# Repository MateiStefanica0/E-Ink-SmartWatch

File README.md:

## 1. Schema bloc

## 2. Descrierea functionalitatii hardware

Sistemul este proiectat in jurul microcontrolerului nRF52840, punand accent pe conectivitate stabila si conservarea energiei, utilizand o tehnologie de afisare E-Paper care permite vizibilitate excelenta in lumina solara cu un consum de curent extrem de mic in starea statica.

### 2.1. Nucleul Sistemului (MCU)
* **Microcontroler:** Nordic nRF52840.
* **Comunicatie:** Gestioneaza functionalitatile Bluetooth si perifericele prin I2C si SPI.
* **Radio:** Semnalul trece printr-o retea de filtrare catre o antena ceramica de 2.4GHz. Sub antena, PCB-ul este decupat pentru a nu bloca semnalul.

### 2.2. Management Energie
* **Incarcare:** Chip-ul BQ25180 gestioneaza incarcarea bateriei LiPo prin mufa USB-C.
* **Monitorizare:** MAX17048 masoara constant nivelul bateriei si transmite datele prin I2C.
* **Regulator:** RT6160A (Buck-Boost) asigura o tensiune constanta de 3.3V, chiar si cand bateria se descarca.

### 2.3. Afisaj si Feedback
* **Ecran E-Paper:** Conectat prin interfata SPI pentru consum minim (consuma energie doar cand schimba imaginea).
* **Circuit Drive:** Include tranzistori si diode pentru a genera tensiunile necesare refresh-ului ecranului.
* **Vibratii:** Driver-ul DRV2605 controleaza motorul haptic, oferind alerte tactile utilizatorului.

### 2.4. Senzori si Protectie
* **Miscare:** Senzorul BMA423 (IMU) este folosit pentru pedometru si detectarea gestului de ridicare a mainii.
* **Protectie USB:** Chip-ul USBLC6-2 protejeaza placa impotriva descarcarilor electrostatice de pe portul USB.

### 2.5. Calcule de consum (estimativ)
* **Sleep Mode:** Consumul sistemului este de aproximativ 2-5 uA (nRF52840 + IMU in low power).
I_sleep = MCU_off + IMU_low + FuelGauge + DC/DC = 1.5 + 7 + 23 + 2 = ~33.5 uA
* **Active Mode:** In timpul transferului de date sau refresh-ului ecranului, consumul poate urca la 5-12 mA.
I_active = MCU_active + IMU_active + EPD_refresh + Haptic = ~10mAh
* **Autonomie:** 
Presupunand ca dintr-o ora, ceasul e activ 2 minute si in standby 58 de minute:
I_mediu = ( (I_active * 2 min) + (I_sleep * 58 min)) / 60 min = ~365 uA

Deci, autonomia e capacitatea_bateriei / I_mediu = 100mAh / 365uA = ~274 ore

## 3. Alocarea Pinilor nRF52840 (Pin Mapping)

Configuratia pinilor a fost aleasa pentru a optimiza rutarea pe PCB si pentru a respecta cerintele perifericelor. Toti pinii sunt configurati in firmware conform tabelului:

| Functie / Periferic | Semnal (Net) | Pin MCU | Explicatie |
| :--- | :--- | :--- | :--- |
| **I2C Bus (SCL)** | `I2C_SCL` | **P0.27** | Bus comun: IMU, Fuel Gauge, Haptic, PMIC. |
| **I2C Bus (SDA)** | `I2C_SDA` | **P0.26** | Bus comun: IMU, Fuel Gauge, Haptic, PMIC. |
| **SPI (SCK)** | `EPD_SCK` | **P0.31** | Ceas pentru transfer date catre ecran. |
| **SPI (MOSI)** | `EPD_MOSI` | **P0.29** | Date imagini catre ecran. |
| **EPD Control** | `EPD_BUSY` | **P0.05** | Indica daca ecranul este ocupat. |
| **EPD Control** | `EPD_RST` | **P0.06** | Reset hardware pentru ecran. |
| **EPD Control** | `EPD_DC` | **P0.08** | Selectie Date sau Comenzi (Data/Command). |
| **Butoane** | `SW_UP` | **P0.11** | Buton SUS (navigare). |
| **Butoane** | `SW_ENT` | **P0.12** | Buton SELECT (confirmare). |
| **Butoane** | `SW_DN` | **P0.14** | Buton JOS (navigare). |
| **Haptic Feedback**| `EN_HAPTIC` | **P0.17** | Activare driver vibratii. |
| **Senzor IMU** | `IMU_INT1` | **P0.19** | Intrerupere pentru detectare miscare. |
| **Debug/Prog** | `SWDIO` | `SWDIO` | Programare si depanare. |
| **Debug/Prog** | `SWCLK` | `SWCLK` | Ceas programare. |

---

## 4. Detalii de Design (Design Log)

### 4.1. Implementare PCB
* **Antena RF:** Plasata pe margine, cu zona de sub ea libera (fara cupru) pentru semnal Bluetooth bun.
* **Grosime:** PCB-ul are 1.0mm grosime pentru a incapea in carcasa InkTime si am ales ca rutarea sa fie pe 4 layere: unul de GND, unul de Power, unul de top si unul de bottom.
* **Filtrare:** Condensatorii de 100nF sunt pusi cat mai aproape de pinii de alimentare ai chip-urilor.
* **Trasee:** Puterea are latime de 0.3mm, iar semnalele de date 0.15mm.
* **Abordare:** Initial, am incercat sa fac autorutare, dar nu a functionat, asa ca apoi am aranjat componentele pe placa pentru a fi cat mai putine fire intre pini indepartati, apoi am rutat semnalele care nu sunt de putere, apoi pe cele de putere, iar la final am pus polygon pour si am tras si ultimele fire de GND ramase.

### 4.2. Carcasa si Erori
* **Aliniere:** Butoanele si mufa USB-C sunt puse exact unde sunt gaurile in carcasa data.
* **Erori permise:** Erorile de tip "Dimension" de la USB si butoane sunt ignorate conform cerintelor proiectului. 
* **Erori ERC:** Singurele erori care au ramas sunt cele legate de pinii de care nu am legat nimic.
* **Erori DRC:** Erorile pe care le-am admis sunt cele cauzate de fire care trec printre alti pini ai microcontrollerului (asta nu se poate evita) sau viasuri care sunt prea apropiate din acelasi motiv.

## 5. Tabel BOM (Bill of Materials)

Mai jos sunt prezentate componentele principale necesare pentru asamblarea ceasului InkTime. Codurile de produs sunt optimizate pentru serviciul de asamblare JLC PCB.

| Designator | Componenta | Descriere / Parametri | Link Achizitie | Datasheet |
| :--- | :--- | :--- | :--- | :--- |
| U1 | **nRF52840** | MCU Bluetooth 5.4, ARM Cortex-M4F | [Link JLC](https://jlcpcb.com/partdetail/NordicSemicon-NRF52840_QIAAR/C190794) | [Datasheet](https://www.lcsc.com/datasheet/lcsc_datasheet_2304140030_Nordic-Semicon-NRF52840-QIAA-R_C190794.pdf) |
| U2 | **BQ25180YBGR** | IC Incarcare Baterie LiPo (I2C) | [Link JLC](https://jlcpcb.com/partdetail/TexasInstruments-BQ25180YBGR/C3682423) | [Datasheet](https://www.ti.com/cn/lit/gpn/bq25180) |
| U3 | **MAX17048G+T10**| Fuel Gauge (Monitorizare baterie) | [Link JLC](https://jlcpcb.com/partdetail/2777647-MAX17048GT10/C2682616) | [Datasheet](https://www.lcsc.com/datasheet/lcsc_datasheet_2410121738_Analog-Devices-Inc--Maxim-Integrated-MAX17048G-T10_C2682616.pdf) |
| IC1 | **RT6160AWSC** | Regulator Buck-Boost 3.3V | [Link JLC](https://jlcpcb.com/partdetail/RichtekTech-RT6160AWSC/C7065276) | [Datasheet](https://wmsc.lcsc.com/wmsc/upload/file/pdf/v2/lcsc/2312271436_Richtek-Tech-RT6160AWSC_C7065276.pdf) |
| IC2 | **BMA423** | Accelerometru 3 axe (IMU) | [Link JLC](https://jlcpcb.com/partdetail/BoschSensortec-BMA423/C189517) | [Datasheet](https://www.lcsc.com/datasheet/lcsc_datasheet_1810010040_Bosch-Sensortec-BMA423_C189517.pdf) |
| IC3 | **DRV2605YZFR** | Driver Motor Haptic (LRA/ERM) | [Link JLC](https://jlcpcb.com/partdetail/TexasInstruments-DRV2605YZFR/C81079) | [Datasheet](https://jlcpcb.com/partdetail/TexasInstruments-DRV2605YZFR/C81079) |
| ANT1 | **2450AT18B100E**| Antena Ceramica 2.4GHz | [Link JLC](https://jlcpcb.com/partdetail/JohansonDielectrics-2450AT18B100E/C2917717) | [Datasheet](https://www.lcsc.com/datasheet/lcsc_datasheet_2404021210_Johanson-Dielectrics-2450AT18B100E_C2917717.pdf) |
| J1 | **KH-TYPE-C-16P** | Conector USB Type-C 16 pini | [Link JLC](https://jlcpcb.com/partdetail/Shenzhen_KinghelmElec-KH_TYPE_C16P/C709357) | [Datasheet](https://jlcpcb.com/partdetail/Shenzhen_KinghelmElec-KH_TYPE_C16P/C709357) |
| J2 | **503480-2400** | Conector FPC 24 pini (E-Paper) | [Link JLC](https://jlcpcb.com/parts/componentSearch?searchTxt=503480-2400) | [Datasheet](https://www.molex.com/content/dam/molex/molex-dot-com/products/automated/en-us/salesdrawingpdf/503/503480/5034802400_sd.pdf?inline) |
| C_dec | **Condensator 100nF** | 0201, X5R, 6.3V (Decuplare generala) | [Link JLC](https://jlcpcb.com/partdetail/SamsungElectroMechanics-CL03A104KQ3NNNC/C1613) | [Datasheet](https://datasheet.lcsc.com/lcsc/1811141213_Samsung-Electro-Mechanics-CL03A104KQ3NNNC_C1613.pdf) |
| C_bulk | **Condensator 10uF** | 0402, X5R, 10V (Filtrare alimentare) | [Link JLC](https://jlcpcb.com/partdetail/MurataElectronics-GRM155R61A106ME11D/C155255) | [Datasheet](https://datasheet.lcsc.com/lcsc/1811011516_Murata-Electronics-GRM155R61A106ME11D_C155255.pdf) |
| R_pu | **Rezistenta 4.7k** | 0201, 1/20W (Pull-up I2C/Butoane) | [Link JLC](https://jlcpcb.com/partdetail/Yageo-RC0201JR074K7L/C13032) | [Datasheet](https://datasheet.lcsc.com/lcsc/1811021213_Yageo-RC0201JR-074K7L_C13032.pdf) |
| L_pwr | **Inductor 1.0uH** | 0805, 2.1A (Pentru RT6160A/Buck-Boost) | [Link JLC](https://jlcpcb.com/partdetail/Sunlord-MWSA0503S1R0MT/C2915000) | [Datasheet](https://datasheet.lcsc.com/lcsc/2203151500_Sunlord-MWSA0503S-1R0MT_C2915000.pdf) |
| X_32k | **Cristal 32.768kHz** | 1.6x1.0mm, 9pF (Pentru Sleep Mode nRF) | [Link JLC](https://jlcpcb.com/partdetail/YangzhouYangjieElectronic-FC1610AN32_7680KA_A/C147814) | [Datasheet](https://datasheet.lcsc.com/lcsc/1811141221_Epson-FC-1610-32-7680KA-A3_C147814.pdf) |
| D_esd | **USBLC6-2P6** | Protectie ESD USB (SOT-666) | [Link JLC](https://jlcpcb.com/partdetail/STMicroelectronics-USBLC62P6/C7519) | [Datasheet](https://www.st.com/resource/en/datasheet/usblc6-2.pdf) |

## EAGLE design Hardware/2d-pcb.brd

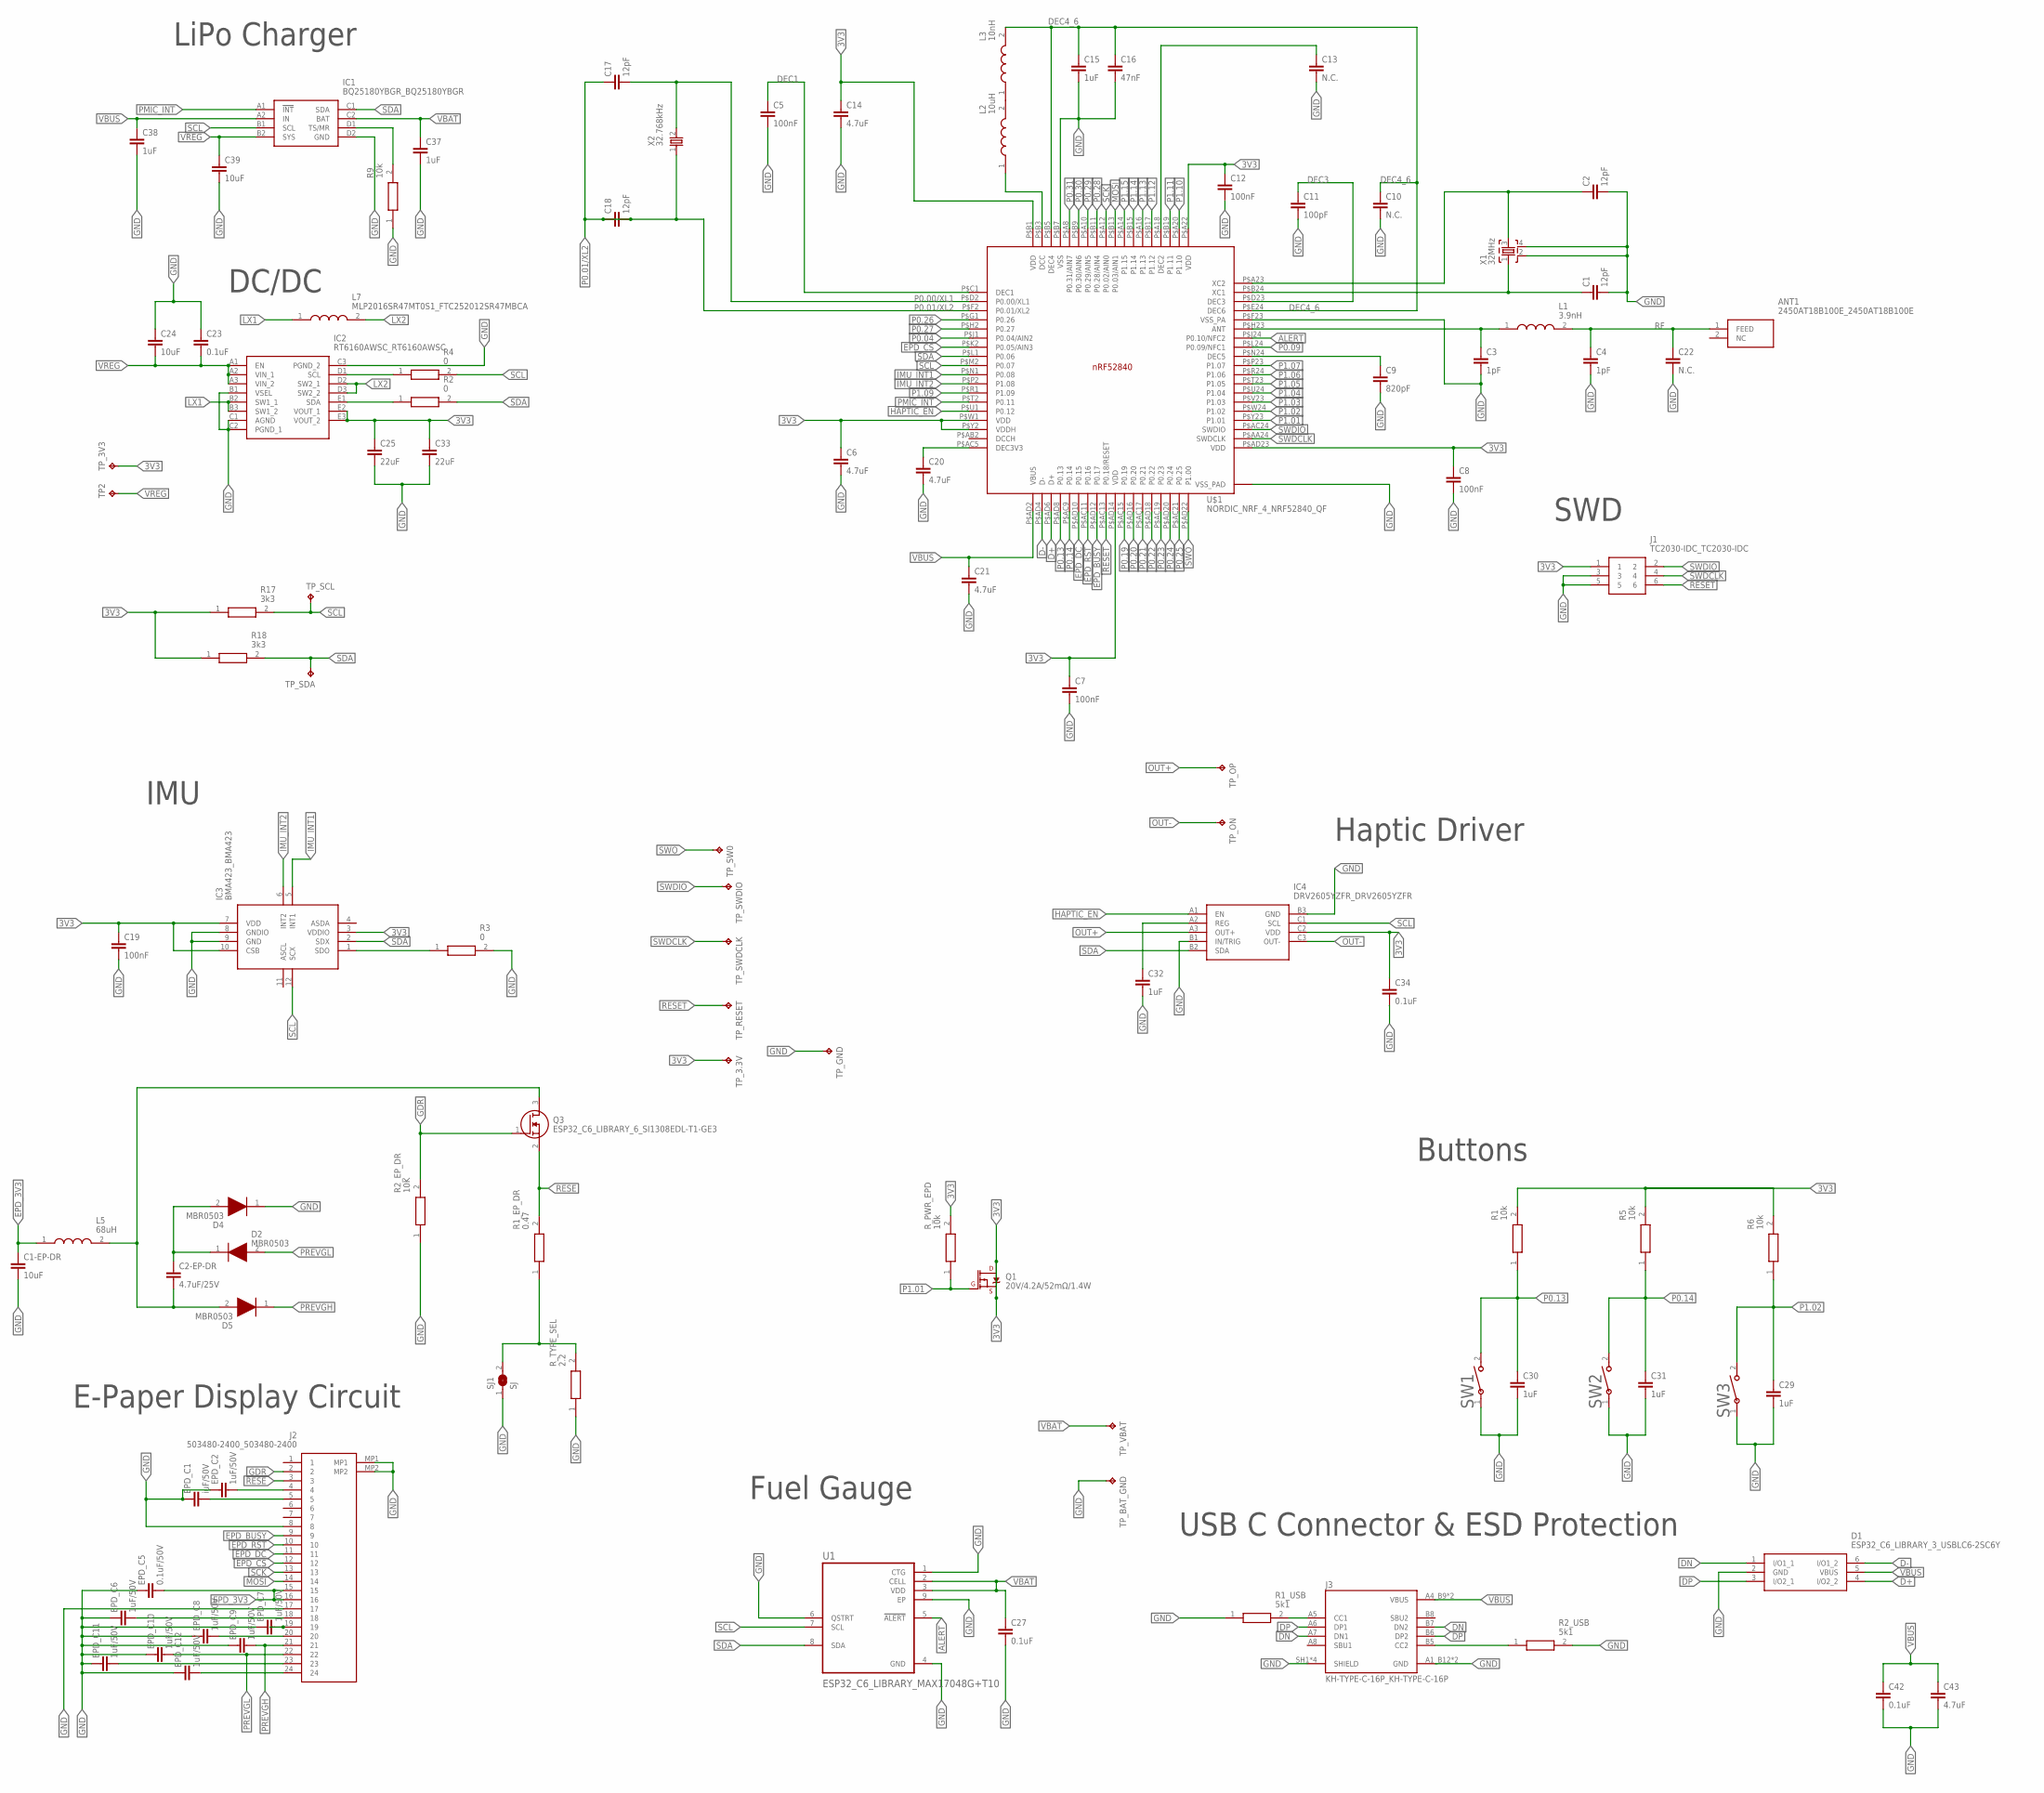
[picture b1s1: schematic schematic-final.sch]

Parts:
ANT1: 2450AT18B100E_2450AT18B100E; 2450AT18B100E_ANTC3216X140N
C1, C2, C17, C18: 12pF; ESP32_C6_LIBRARY_1_ESP32_WROVER_EAGLE-LTSPICE_C0402
C1-EP-DR, C24, C39: 10uF; ESP32_C6_LIBRARY_1_ESP32_WROVER_EAGLE-LTSPICE_C0402
C2-EP-DR: 4.7uF/25V; ESP32_C6_LIBRARY_1_ESP32_WROVER_EAGLE-LTSPICE_C0402
C3, C4: 1pF; ESP32_C6_LIBRARY_1_ESP32_WROVER_EAGLE-LTSPICE_C0402
C5, C7, C8, C12, C19: 100nF; NORDIC_NRF_3_RESC0201_L
C6, C14, C20, C21, C43: 4.7uF; ESP32_C6_LIBRARY_1_ESP32_WROVER_EAGLE-LTSPICE_C0402
C9: 820pF; ESP32_C6_LIBRARY_1_ESP32_WROVER_EAGLE-LTSPICE_C0402
C10, C13, C22: N.C.; ESP32_C6_LIBRARY_1_ESP32_WROVER_EAGLE-LTSPICE_C0402
C11: 100pF; ESP32_C6_LIBRARY_1_ESP32_WROVER_EAGLE-LTSPICE_C0402
C15, C29, C30, C31, C32, C37, C38: 1uF; ESP32_C6_LIBRARY_1_ESP32_WROVER_EAGLE-LTSPICE_C0402
C16: 47nF; ESP32_C6_LIBRARY_1_ESP32_WROVER_EAGLE-LTSPICE_C0402
C23, C27, C34, C42: 0.1uF; ESP32_C6_LIBRARY_1_ESP32_WROVER_EAGLE-LTSPICE_C0402
C25, C33: 22uF; ESP32_C6_LIBRARY_1_ESP32_WROVER_EAGLE-LTSPICE_C0402
D1: ESP32_C6_LIBRARY_3_USBLC6-2SC6Y; ESP32_C6_LIBRARY_3_SOT95P280X145-6N
D2, D4, D5: MBR0503; ESP32_C6_LIBRARY_5_SOD3716X135N
EPD_C1: iuF/50V; ESP32_C6_LIBRARY_1_ESP32_WROVER_EAGLE-LTSPICE_C0402
EPD_C2, EPD_C6, EPD_C7, EPD_C8, EPD_C9, EPD_C10, EPD_C11, EPD_C12: 1uF/50V; ESP32_C6_LIBRARY_1_ESP32_WROVER_EAGLE-LTSPICE_C0402
EPD_C5: 0.1uF/50V; ESP32_C6_LIBRARY_1_ESP32_WROVER_EAGLE-LTSPICE_C0402
IC1: BQ25180YBGR_BQ25180YBGR; BQ25180YBGR_BGA8C40P2X4_100X155X50
IC2: RT6160AWSC_RT6160AWSC; RT6160AWSC_BGA15C40P3X5_140X230X60
IC3: BMA423_BMA423
IC4: DRV2605YZFR_DRV2605YZFR; DRV2605YZFR_BGA9C50P3X3_144X144X62
J1: TC2030-IDC_TC2030-IDC; TC2030-IDC_TC2030IDC
J2: 503480-2400_503480-2400; 503480-2400_5034802400
J3: KH-TYPE-C-16P_KH-TYPE-C-16P; KH-TYPE-C-16P_KINGHELM_KH-TYPE-C-16P
L1: 3.9nH; MLP2016SR47MT0S1_INDC2016X100N
L2: 10uH; MLP2016SR47MT0S1_INDC2016X100N
L3: 10nH; MLP2016SR47MT0S1_INDC2016X100N
L5: 68uH; MLP2016SR47MT0S1_INDC2016X100N
L7: MLP2016SR47MT0S1_FTC252012SR47MBCA; MLP2016SR47MT0S1_INDC2016X100N
Q1: 20V/4.2A/52mΩ/1.4W; ESP32_C6_LIBRARY_4_ESP32_C6_LIBRARY_4_ESP32_C6_LIBRARY_4_ES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
Q3: ESP32_C6_LIBRARY_6_SI1308EDL-T1-GE3; ESP32_C6_LIBRARY_6_SOT65P210X110-3N
R1, R5, R6: 10k; ERA-1AEB3401C_0201
R1_EP_DR: 0.47; ERA-1AEB3401C_0201
R1_USB, R2_USB: 5k1; ERA-1AEB3401C_0201
R2, R3, R4: 0; ERA-1AEB3401C_0201
R2_EP_DR: 10K; ERA-1AEB3401C_0201
R9: 10k; CPF0201D7K68C1_0201
R17, R18: 3k3; ERA-1AEB3401C_0201
R_PWR_EPD: 10k; ERA-1AEB3401C_0201
R_TYPE_SEL: 2.2; ERA-1AEB3401C_0201
SJ1: SJ; ESP32_C6_LIBRARY_7_JUMPER_SJ
SW1, SW2, SW3: 2025-10-22_07-23-44_LIBRARY_EVP-AKE31ASW_EVP-AKE3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; 2025-10-22_07-23-44_LIBRARY_SW_EVP-AKE31A_PAN
TP2: HECTOR_WATCH_1_TPTP20R; HECTOR_WATCH_1_TP20R
TP_3.3V, TP_3V3: HECTOR_WATCH_1_TPTP20R; HECTOR_WATCH_1_TP20R
TP_BAT_GND: HECTOR_WATCH_1_TPTP20R; HECTOR_WATCH_1_TP20R
TP_GND: HECTOR_WATCH_1_TPTP20R; HECTOR_WATCH_1_TP20R
TP_ON: HECTOR_WATCH_1_TPTP20R; HECTOR_WATCH_1_TP20R
TP_OP: HECTOR_WATCH_1_TPTP20R; HECTOR_WATCH_1_TP20R
TP_RESET: HECTOR_WATCH_1_TPTP20R; HECTOR_WATCH_1_TP20R
TP_SCL: HECTOR_WATCH_1_TPTP20R; HECTOR_WATCH_1_TP20R
TP_SDA: HECTOR_WATCH_1_TPTP20R; HECTOR_WATCH_1_TP20R
TP_SW0: HECTOR_WATCH_1_TPTP20R; HECTOR_WATCH_1_TP20R
TP_SWDCLK: HECTOR_WATCH_1_TPTP20R; HECTOR_WATCH_1_TP20R
TP_SWDIO: HECTOR_WATCH_1_TPTP20R; HECTOR_WATCH_1_TP20R
TP_VBAT: HECTOR_WATCH_1_TPTP20R; HECTOR_WATCH_1_TP20R
U1: ESP32_C6_LIBRARY_MAX17048G+T10; ESP32_C6_LIBRARY_SON50P200X200X80-9N
U$1: NORDIC_NRF_4_NRF52840_QF; NORDIC_NRF_4_AQFN50P700X700X85_HS-74N
X1: 32MHz; NORDIC_NRF_BT-XTAL_2016_N
X2: 32.768kHz; NORDIC_NRF_1_XTAL_3215_N

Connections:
3V3: C6.1, C7.1, C8.1, C12.1, C14.1, C19.1, C25.1, C33.1, C34.1, IC2.E2 (VOUT_1), IC2.E3 (VOUT_2), IC3.3 (VDDIO), IC3.7 (VDD), IC3.10 (CSB), IC4.C2 (VDD), J1.1, Q1.2 (S), Q1.3 (D), R1.2, R5.2, R6.2, R17.1, R18.1, R_PWR_EPD.2, TP_3.3V.TP, TP_3V3.TP, U$1.P$A22 (VDD), U$1.P$AD14 (VDD), U$1.P$AD23 (VDD), U$1.P$B1 (VDD), U$1.P$W1 (VDD), U$1.P$Y2 (VDDH)
ALERT: U1.5 (!ALERT), U$1.P$J24 (P0.10/NFC2)
D+: D1.4 (I/O2_2), U$1.P$AD6 (D+)
D-: D1.6 (I/O1_2), U$1.P$AD4 (D-)
DEC1: C5.1, U$1.P$C1 (DEC1)
DEC3: C11.1, U$1.P$D23 (DEC3)
DEC4_6: C10.1, C15.1, C16.1, L3.2, U$1.P$B5 (DEC4), U$1.P$E24 (DEC6)
DN: D1.1 (I/O1_1), J3.A7 (DN1), J3.B7 (DN2)
DP: D1.3 (I/O2_1), J3.A6 (DP1), J3.B6 (DP2)
EPD_3V3: C1-EP-DR.1, EPD_C5.2, J2.15, J2.16, L5.1
EPD_BUSY: J2.9, U$1.P$AD12 (P0.17)
EPD_CS: J2.12, U$1.P$K2 (P0.05/AIN3)
EPD_DC: J2.11, U$1.P$AD10 (P0.15)
EPD_RST: J2.10, U$1.P$AC11 (P0.16)
GDR: J2.2, Q3.1 (G), R2_EP_DR.2
GND: C1.2, C1-EP-DR.2, C2.2, C3.2, C4.2, C5.2, C6.2, C7.2, C8.2, C9.2, C10.2, C11.2, C12.2, C13.2, C14.2, C15.2, C16.2, C19.2, C20.2, C21.2, C22.2, C23.1, C24.1, C25.2, C27.2, C29.2, C30.2, C31.2, C32.2, C33.2, C34.2, C37.2, C38.2, C39.2, C42.2, C43.2, D1.2 (GND), D4.1 (K), EPD_C1.1, EPD_C2.1, EPD_C5.1, EPD_C6.1, EPD_C7.1, EPD_C8.1, EPD_C9.1, EPD_C10.1, EPD_C11.1, EPD_C12.1, IC1.D2 (GND), IC2.B1 (VSEL), IC2.C1 (AGND), IC2.C2 (PGND_1), IC2.C3 (PGND_2), IC3.8 (GNDIO), IC3.9 (GND), IC4.B1 (IN/TRIG), IC4.B3 (GND), J1.3, J1.5, J2.8, J2.17, J2.MP1, J2.MP2, J3.A1_B12 (GND), J3.A12_B1 (GND), J3.SH1 (SHIELD), J3.SH2 (SHIELD), J3.SH3 (SHIELD), J3.SH4 (SHIELD), R1_USB.1, R2_EP_DR.1, R2_USB.2, R3.2, R9.1, R_TYPE_SEL.1, SJ1.1, SW1.1, SW2.1, SW3.1, TP_BAT_GND.TP, TP_GND.TP, U1.1 (CTG), U1.4 (GND), U1.6 (QSTRT), U1.9 (EP), U$1.P$74 (VSS_PAD), U$1.P$75 (VSS_PAD), U$1.P$76 (VSS_PAD), U$1.P$77 (VSS_PAD), U$1.P$78 (VSS_PAD), U$1.P$79 (VSS_PAD), U$1.P$80 (VSS_PAD), U$1.P$81 (VSS_PAD), U$1.P$82 (VSS_PAD), U$1.P$83 (VSS_PAD)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
HAPTIC_EN: IC4.A1 (EN), U$1.P$U1 (P0.12)
IMU_INT1: IC3.5 (INT1), U$1.P$N1 (P0.08)
IMU_INT2: IC3.6 (INT2), U$1.P$P2 (P1.08)
LX1: IC2.B2 (SW1_1), IC2.B3 (SW1_2), L7.1
LX2: IC2.D2 (SW2_1), IC2.D3 (SW2_2), L7.2
MOSI: J2.14, U$1.P$B13 (P0.03/AIN1)
unnamed: IC3.1 (SDO), R3.1
unnamed: IC2.D1 (SCL), R4.1
unnamed: IC1.D1 (TS/MR), R9.2
unnamed: IC2.E1 (SDA), R2.1
unnamed: C20.1, U$1.P$AC5 (DEC3V3)
unnamed: C9.1, U$1.P$N24 (DEC5)
unnamed: C3.1, L1.1, U$1.P$H23 (ANT)
unnamed: C13.1, U$1.P$A18 (DEC2)
unnamed: C2-EP-DR.2, D5.2 (A), L5.2, Q3.3 (D)
unnamed: L2.1, U$1.P$B3 (DCC)
unnamed: C2.1, U$1.P$A23 (XC2), X1.3
unnamed: C1.1, U$1.P$B24 (XC1), X1.1
unnamed: L2.2, L3.1
unnamed: R1_EP_DR.1, R_TYPE_SEL.2, SJ1.2
unnamed: C2-EP-DR.1, D2.1 (K), D4.2 (A)
unnamed: C32.1, IC4.A2 (REG)
unnamed: EPD_C2.2, J2.4
unnamed: EPD_C1.2, J2.5
unnamed: EPD_C6.2, J2.18
unnamed: EPD_C7.2, J2.19
unnamed: EPD_C8.2, J2.20
unnamed: EPD_C11.2, J2.23
unnamed: EPD_C12.2, J2.24
unnamed: J3.B5 (CC2), R2_USB.1
unnamed: J3.A5 (CC1), R1_USB.2
OUT+: IC4.A3 (OUT+), TP_OP.TP
OUT-: IC4.C3 (OUT-), TP_ON.TP
P0.00/XL1: C17.2, U$1.P$D2 (P0.00/XL1), X2.2
P0.01/XL2: C17.1, C18.1, C18.2, U$1.P$F2 (P0.01/XL2), X2.1
P0.04: U$1.P$J1 (P0.04/AIN2)
P0.09: U$1.P$L24 (P0.09/NFC1)
P0.13: C30.1, R1.1, SW1.2, U$1.P$AD8 (P0.13)
P0.14: C31.1, R5.1, SW2.2, U$1.P$AC9 (P0.14)
P0.19: U$1.P$AC15 (P0.19)
P0.20: U$1.P$AD16 (P0.20)
P0.21: U$1.P$AC17 (P0.21)
P0.22: U$1.P$AD18 (P0.22)
P0.23: U$1.P$AC19 (P0.23)
P0.24: U$1.P$AD20 (P0.24)
P0.25: U$1.P$AC21 (P0.25)
P0.26: U$1.P$G1 (P0.26)
P0.27: U$1.P$H2 (P0.27)
P0.28: U$1.P$B11 (P0.28/AIN4)
P0.29: U$1.P$A10 (P0.29/AIN5)
P0.30: U$1.P$B9 (P0.30/AIN6)
P0.31: U$1.P$A8 (P0.31/AIN7)
P1.01: Q1.1 (G), R_PWR_EPD.1, U$1.P$Y23 (P1.01)
P1.02: C29.1, R6.1, SW3.2, U$1.P$W24 (P1.02)
P1.03: U$1.P$V23 (P1.03)
P1.04: U$1.P$U24 (P1.04)
P1.05: U$1.P$T23 (P1.05)
P1.06: U$1.P$R24 (P1.06)
P1.07: U$1.P$P23 (P1.07)
P1.09: U$1.P$R1 (P1.09)
P1.10: U$1.P$A20 (P1.10)
P1.11: U$1.P$B19 (P1.11)
P1.12: U$1.P$B17 (P1.12)
P1.13: U$1.P$A16 (P1.13)
P1.14: U$1.P$B15 (P1.14)
P1.15: U$1.P$A14 (P1.15)
PMIC_INT: IC1.A1 (!INT), U$1.P$T2 (P0.11)
PREVGH: D5.1 (K), EPD_C9.2, J2.21
PREVGL: D2.2 (A), EPD_C10.2, J2.22
RESE: J2.3, Q3.2 (S), R1_EP_DR.2
RESET: J1.6, TP_RESET.TP, U$1.P$AC13 (P0.18/RESET)
RF: ANT1.1 (FEED), C4.1, C22.1, L1.2
SCK: J2.13, U$1.P$A12 (P0.02/AIN0)
SCL: IC1.B1 (SCL), IC3.12 (SCX), IC4.C1 (SCL), R4.2, R17.2, TP_SCL.TP, U1.7 (SCL), U$1.P$M2 (P0.07)
SDA: IC1.C1 (SDA), IC3.2 (SDX), IC4.B2 (SDA), R2.2, R18.2, TP_SDA.TP, U1.8 (SDA), U$1.P$L1 (P0.06)
SWDCLK: J1.4, TP_SWDCLK.TP, U$1.P$AC24 (SWDIO)
SWDIO: J1.2, TP_SWDIO.TP, U$1.P$AA24 (SWDCLK)
SWO: TP_SW0.TP, U$1.P$AD22 (P1.00)
VBAT: C27.1, C37.1, IC1.C2 (BAT), TP_VBAT.TP, U1.2 (CELL), U1.3 (VDD)
VBUS: C21.1, C38.1, C42.1, C43.1, D1.5 (VBUS), IC1.A2 (IN), J3.A4_B9 (VBUS), J3.A9_B4 (VBUS), U$1.P$AD2 (VBUS)
VREG: C23.2, C24.2, C39.1, IC1.B2 (SYS), IC2.A1 (EN), IC2.A2 (VIN_1), IC2.A3 (VIN_2), TP2.TP

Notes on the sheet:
LiPo Charger
DC/DC
IMU
SWD
Haptic Driver
E-Paper Display Circuit
Fuel Gauge
USB C Connector & ESD Protection
Buttons

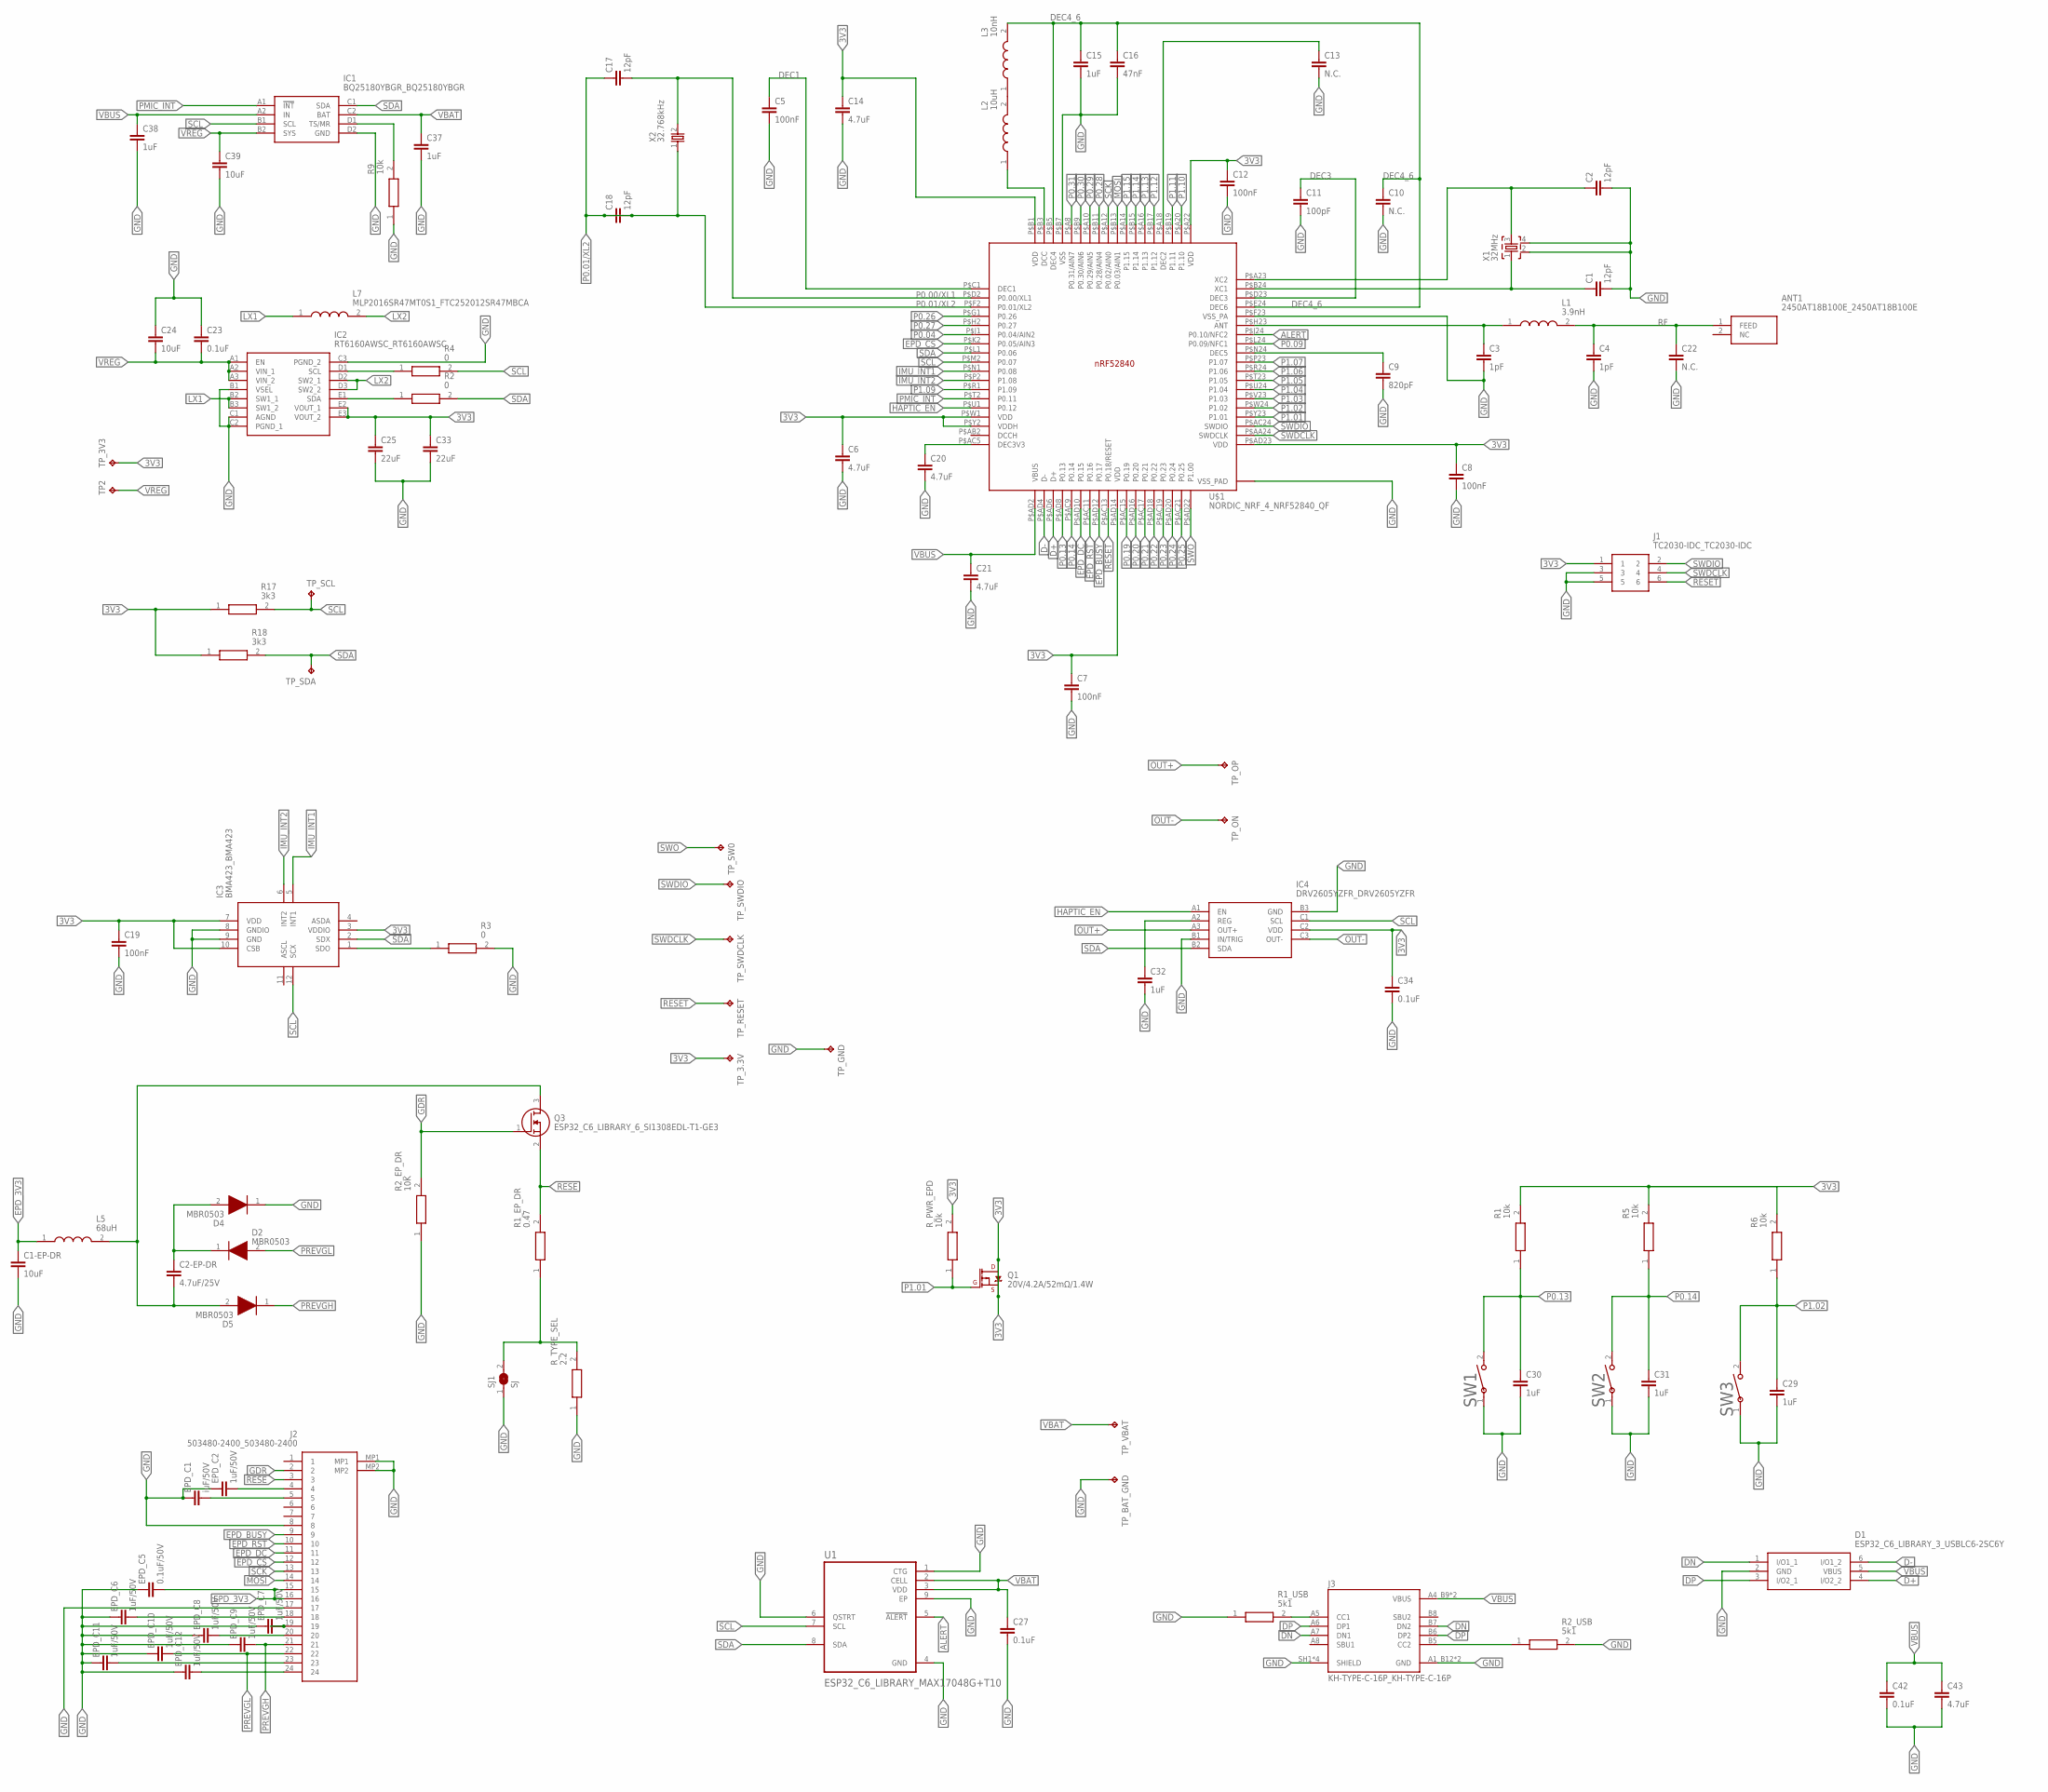
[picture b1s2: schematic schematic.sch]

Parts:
ANT1: 2450AT18B100E_2450AT18B100E; 2450AT18B100E_ANTC3216X140N
C1, C2, C17, C18: 12pF; ESP32_C6_LIBRARY_1_ESP32_WROVER_EAGLE-LTSPICE_C0402
C1-EP-DR, C24, C39: 10uF; ESP32_C6_LIBRARY_1_ESP32_WROVER_EAGLE-LTSPICE_C0402
C2-EP-DR: 4.7uF/25V; ESP32_C6_LIBRARY_1_ESP32_WROVER_EAGLE-LTSPICE_C0402
C3, C4: 1pF; ESP32_C6_LIBRARY_1_ESP32_WROVER_EAGLE-LTSPICE_C0402
C5, C7, C8, C12, C19: 100nF; NORDIC_NRF_3_RESC0201_L
C6, C14, C20, C21, C43: 4.7uF; ESP32_C6_LIBRARY_1_ESP32_WROVER_EAGLE-LTSPICE_C0402
C9: 820pF; ESP32_C6_LIBRARY_1_ESP32_WROVER_EAGLE-LTSPICE_C0402
C10, C13, C22: N.C.; ESP32_C6_LIBRARY_1_ESP32_WROVER_EAGLE-LTSPICE_C0402
C11: 100pF; ESP32_C6_LIBRARY_1_ESP32_WROVER_EAGLE-LTSPICE_C0402
C15, C29, C30, C31, C32, C37, C38: 1uF; ESP32_C6_LIBRARY_1_ESP32_WROVER_EAGLE-LTSPICE_C0402
C16: 47nF; ESP32_C6_LIBRARY_1_ESP32_WROVER_EAGLE-LTSPICE_C0402
C23, C27, C34, C42: 0.1uF; ESP32_C6_LIBRARY_1_ESP32_WROVER_EAGLE-LTSPICE_C0402
C25, C33: 22uF; ESP32_C6_LIBRARY_1_ESP32_WROVER_EAGLE-LTSPICE_C0402
D1: ESP32_C6_LIBRARY_3_USBLC6-2SC6Y; ESP32_C6_LIBRARY_3_SOT95P280X145-6N
D2, D4, D5: MBR0503; ESP32_C6_LIBRARY_5_SOD3716X135N
EPD_C1: iuF/50V; ESP32_C6_LIBRARY_1_ESP32_WROVER_EAGLE-LTSPICE_C0402
EPD_C2, EPD_C6, EPD_C7, EPD_C8, EPD_C9, EPD_C10, EPD_C11, EPD_C12: 1uF/50V; ESP32_C6_LIBRARY_1_ESP32_WROVER_EAGLE-LTSPICE_C0402
EPD_C5: 0.1uF/50V; ESP32_C6_LIBRARY_1_ESP32_WROVER_EAGLE-LTSPICE_C0402
IC1: BQ25180YBGR_BQ25180YBGR; BQ25180YBGR_BGA8C40P2X4_100X155X50
IC2: RT6160AWSC_RT6160AWSC; RT6160AWSC_BGA15C40P3X5_140X230X60
IC3: BMA423_BMA423
IC4: DRV2605YZFR_DRV2605YZFR; DRV2605YZFR_BGA9C50P3X3_144X144X62
J1: TC2030-IDC_TC2030-IDC; TC2030-IDC_TC2030IDC
J2: 503480-2400_503480-2400; 503480-2400_5034802400
J3: KH-TYPE-C-16P_KH-TYPE-C-16P; KH-TYPE-C-16P_KINGHELM_KH-TYPE-C-16P
L1: 3.9nH; MLP2016SR47MT0S1_INDC2016X100N
L2: 10uH; MLP2016SR47MT0S1_INDC2016X100N
L3: 10nH; MLP2016SR47MT0S1_INDC2016X100N
L5: 68uH; MLP2016SR47MT0S1_INDC2016X100N
L7: MLP2016SR47MT0S1_FTC252012SR47MBCA; MLP2016SR47MT0S1_INDC2016X100N
Q1: 20V/4.2A/52mΩ/1.4W; ESP32_C6_LIBRARY_4_ESP32_C6_LIBRARY_4_ESP32_C6_LIBRARY_4_ES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
Q3: ESP32_C6_LIBRARY_6_SI1308EDL-T1-GE3; ESP32_C6_LIBRARY_6_SOT65P210X110-3N
R1, R5, R6: 10k; ERA-1AEB3401C_0201
R1_EP_DR: 0.47; ERA-1AEB3401C_0201
R1_USB, R2_USB: 5k1; ERA-1AEB3401C_0201
R2, R3, R4: 0; ERA-1AEB3401C_0201
R2_EP_DR: 10K; ERA-1AEB3401C_0201
R9: 10k; CPF0201D7K68C1_0201
R17, R18: 3k3; ERA-1AEB3401C_0201
R_PWR_EPD: 10k; ERA-1AEB3401C_0201
R_TYPE_SEL: 2.2; ERA-1AEB3401C_0201
SJ1: SJ; ESP32_C6_LIBRARY_7_JUMPER_SJ
SW1, SW2, SW3: 2025-10-22_07-23-44_LIBRARY_EVP-AKE31ASW_EVP-AKE3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; 2025-10-22_07-23-44_LIBRARY_SW_EVP-AKE31A_PAN
TP2: HECTOR_WATCH_1_TPTP20R; HECTOR_WATCH_1_TP20R
TP_3.3V, TP_3V3: HECTOR_WATCH_1_TPTP20R; HECTOR_WATCH_1_TP20R
TP_BAT_GND: HECTOR_WATCH_1_TPTP20R; HECTOR_WATCH_1_TP20R
TP_GND: HECTOR_WATCH_1_TPTP20R; HECTOR_WATCH_1_TP20R
TP_ON: HECTOR_WATCH_1_TPTP20R; HECTOR_WATCH_1_TP20R
TP_OP: HECTOR_WATCH_1_TPTP20R; HECTOR_WATCH_1_TP20R
TP_RESET: HECTOR_WATCH_1_TPTP20R; HECTOR_WATCH_1_TP20R
TP_SCL: HECTOR_WATCH_1_TPTP20R; HECTOR_WATCH_1_TP20R
TP_SDA: HECTOR_WATCH_1_TPTP20R; HECTOR_WATCH_1_TP20R
TP_SW0: HECTOR_WATCH_1_TPTP20R; HECTOR_WATCH_1_TP20R
TP_SWDCLK: HECTOR_WATCH_1_TPTP20R; HECTOR_WATCH_1_TP20R
TP_SWDIO: HECTOR_WATCH_1_TPTP20R; HECTOR_WATCH_1_TP20R
TP_VBAT: HECTOR_WATCH_1_TPTP20R; HECTOR_WATCH_1_TP20R
U1: ESP32_C6_LIBRARY_MAX17048G+T10; ESP32_C6_LIBRARY_SON50P200X200X80-9N
U$1: NORDIC_NRF_4_NRF52840_QF; NORDIC_NRF_4_AQFN50P700X700X85_HS-74N
X1: 32MHz; NORDIC_NRF_BT-XTAL_2016_N
X2: 32.768kHz; NORDIC_NRF_1_XTAL_3215_N

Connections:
3V3: C6.1, C7.1, C8.1, C12.1, C14.1, C19.1, C25.1, C33.1, C34.1, IC2.E2 (VOUT_1), IC2.E3 (VOUT_2), IC3.3 (VDDIO), IC3.7 (VDD), IC3.10 (CSB), IC4.C2 (VDD), J1.1, Q1.2 (S), Q1.3 (D), R1.2, R5.2, R6.2, R17.1, R18.1, R_PWR_EPD.2, TP_3.3V.TP, TP_3V3.TP, U$1.P$A22 (VDD), U$1.P$AD14 (VDD), U$1.P$AD23 (VDD), U$1.P$B1 (VDD), U$1.P$W1 (VDD), U$1.P$Y2 (VDDH)
ALERT: U1.5 (!ALERT), U$1.P$J24 (P0.10/NFC2)
D+: D1.4 (I/O2_2), U$1.P$AD6 (D+)
D-: D1.6 (I/O1_2), U$1.P$AD4 (D-)
DEC1: C5.1, U$1.P$C1 (DEC1)
DEC3: C11.1, U$1.P$D23 (DEC3)
DEC4_6: C10.1, C15.1, C16.1, L3.2, U$1.P$B5 (DEC4), U$1.P$E24 (DEC6)
DN: D1.1 (I/O1_1), J3.A7 (DN1), J3.B7 (DN2)
DP: D1.3 (I/O2_1), J3.A6 (DP1), J3.B6 (DP2)
EPD_3V3: C1-EP-DR.1, EPD_C5.2, J2.15, J2.16, L5.1
EPD_BUSY: J2.9, U$1.P$AD12 (P0.17)
EPD_CS: J2.12, U$1.P$K2 (P0.05/AIN3)
EPD_DC: J2.11, U$1.P$AD10 (P0.15)
EPD_RST: J2.10, U$1.P$AC11 (P0.16)
GDR: J2.2, Q3.1 (G), R2_EP_DR.2
GND: C1.2, C1-EP-DR.2, C2.2, C3.2, C4.2, C5.2, C6.2, C7.2, C8.2, C9.2, C10.2, C11.2, C12.2, C13.2, C14.2, C15.2, C16.2, C19.2, C20.2, C21.2, C22.2, C23.1, C24.1, C25.2, C27.2, C29.2, C30.2, C31.2, C32.2, C33.2, C34.2, C37.2, C38.2, C39.2, C42.2, C43.2, D1.2 (GND), D4.1 (K), EPD_C1.1, EPD_C2.1, EPD_C5.1, EPD_C6.1, EPD_C7.1, EPD_C8.1, EPD_C9.1, EPD_C10.1, EPD_C11.1, EPD_C12.1, IC1.D2 (GND), IC2.B1 (VSEL), IC2.C1 (AGND), IC2.C2 (PGND_1), IC2.C3 (PGND_2), IC3.8 (GNDIO), IC3.9 (GND), IC4.B1 (IN/TRIG), IC4.B3 (GND), J1.3, J1.5, J2.8, J2.17, J2.MP1, J2.MP2, J3.A1_B12 (GND), J3.A12_B1 (GND), J3.SH1 (SHIELD), J3.SH2 (SHIELD), J3.SH3 (SHIELD), J3.SH4 (SHIELD), R1_USB.1, R2_EP_DR.1, R2_USB.2, R3.2, R9.1, R_TYPE_SEL.1, SJ1.1, SW1.1, SW2.1, SW3.1, TP_BAT_GND.TP, TP_GND.TP, U1.1 (CTG), U1.4 (GND), U1.6 (QSTRT), U1.9 (EP), U$1.P$74 (VSS_PAD), U$1.P$75 (VSS_PAD), U$1.P$76 (VSS_PAD), U$1.P$77 (VSS_PAD), U$1.P$78 (VSS_PAD), U$1.P$79 (VSS_PAD), U$1.P$80 (VSS_PAD), U$1.P$81 (VSS_PAD), U$1.P$82 (VSS_PAD), U$1.P$83 (VSS_PAD)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
HAPTIC_EN: IC4.A1 (EN), U$1.P$U1 (P0.12)
IMU_INT1: IC3.5 (INT1), U$1.P$N1 (P0.08)
IMU_INT2: IC3.6 (INT2), U$1.P$P2 (P1.08)
LX1: IC2.B2 (SW1_1), IC2.B3 (SW1_2), L7.1
LX2: IC2.D2 (SW2_1), IC2.D3 (SW2_2), L7.2
MOSI: J2.14, U$1.P$B13 (P0.03/AIN1)
unnamed: IC3.1 (SDO), R3.1
unnamed: IC2.D1 (SCL), R4.1
unnamed: IC1.D1 (TS/MR), R9.2
unnamed: IC2.E1 (SDA), R2.1
unnamed: C20.1, U$1.P$AC5 (DEC3V3)
unnamed: C9.1, U$1.P$N24 (DEC5)
unnamed: C3.1, L1.1, U$1.P$H23 (ANT)
unnamed: C13.1, U$1.P$A18 (DEC2)
unnamed: C2-EP-DR.2, D5.2 (A), L5.2, Q3.3 (D)
unnamed: L2.1, U$1.P$B3 (DCC)
unnamed: C2.1, U$1.P$A23 (XC2), X1.3
unnamed: C1.1, U$1.P$B24 (XC1), X1.1
unnamed: L2.2, L3.1
unnamed: R1_EP_DR.1, R_TYPE_SEL.2, SJ1.2
unnamed: C2-EP-DR.1, D2.1 (K), D4.2 (A)
unnamed: C32.1, IC4.A2 (REG)
unnamed: EPD_C2.2, J2.4
unnamed: EPD_C1.2, J2.5
unnamed: EPD_C6.2, J2.18
unnamed: EPD_C7.2, J2.19
unnamed: EPD_C8.2, J2.20
unnamed: EPD_C11.2, J2.23
unnamed: EPD_C12.2, J2.24
unnamed: J3.B5 (CC2), R2_USB.1
unnamed: J3.A5 (CC1), R1_USB.2
OUT+: IC4.A3 (OUT+), TP_OP.TP
OUT-: IC4.C3 (OUT-), TP_ON.TP
P0.00/XL1: C17.2, U$1.P$D2 (P0.00/XL1), X2.2
P0.01/XL2: C17.1, C18.1, C18.2, U$1.P$F2 (P0.01/XL2), X2.1
P0.04: U$1.P$J1 (P0.04/AIN2)
P0.09: U$1.P$L24 (P0.09/NFC1)
P0.13: C30.1, R1.1, SW1.2, U$1.P$AD8 (P0.13)
P0.14: C31.1, R5.1, SW2.2, U$1.P$AC9 (P0.14)
P0.19: U$1.P$AC15 (P0.19)
P0.20: U$1.P$AD16 (P0.20)
P0.21: U$1.P$AC17 (P0.21)
P0.22: U$1.P$AD18 (P0.22)
P0.23: U$1.P$AC19 (P0.23)
P0.24: U$1.P$AD20 (P0.24)
P0.25: U$1.P$AC21 (P0.25)
P0.26: U$1.P$G1 (P0.26)
P0.27: U$1.P$H2 (P0.27)
P0.28: U$1.P$B11 (P0.28/AIN4)
P0.29: U$1.P$A10 (P0.29/AIN5)
P0.30: U$1.P$B9 (P0.30/AIN6)
P0.31: U$1.P$A8 (P0.31/AIN7)
P1.01: Q1.1 (G), R_PWR_EPD.1, U$1.P$Y23 (P1.01)
P1.02: C29.1, R6.1, SW3.2, U$1.P$W24 (P1.02)
P1.03: U$1.P$V23 (P1.03)
P1.04: U$1.P$U24 (P1.04)
P1.05: U$1.P$T23 (P1.05)
P1.06: U$1.P$R24 (P1.06)
P1.07: U$1.P$P23 (P1.07)
P1.09: U$1.P$R1 (P1.09)
P1.10: U$1.P$A20 (P1.10)
P1.11: U$1.P$B19 (P1.11)
P1.12: U$1.P$B17 (P1.12)
P1.13: U$1.P$A16 (P1.13)
P1.14: U$1.P$B15 (P1.14)
P1.15: U$1.P$A14 (P1.15)
PMIC_INT: IC1.A1 (!INT), U$1.P$T2 (P0.11)
PREVGH: D5.1 (K), EPD_C9.2, J2.21
PREVGL: D2.2 (A), EPD_C10.2, J2.22
RESE: J2.3, Q3.2 (S), R1_EP_DR.2
RESET: J1.6, TP_RESET.TP, U$1.P$AC13 (P0.18/RESET)
RF: ANT1.1 (FEED), C4.1, C22.1, L1.2
SCK: J2.13, U$1.P$A12 (P0.02/AIN0)
SCL: IC1.B1 (SCL), IC3.12 (SCX), IC4.C1 (SCL), R4.2, R17.2, TP_SCL.TP, U1.7 (SCL), U$1.P$M2 (P0.07)
SDA: IC1.C1 (SDA), IC3.2 (SDX), IC4.B2 (SDA), R2.2, R18.2, TP_SDA.TP, U1.8 (SDA), U$1.P$L1 (P0.06)
SWDCLK: J1.4, TP_SWDCLK.TP, U$1.P$AC24 (SWDIO)
SWDIO: J1.2, TP_SWDIO.TP, U$1.P$AA24 (SWDCLK)
SWO: TP_SW0.TP, U$1.P$AD22 (P1.00)
VBAT: C27.1, C37.1, IC1.C2 (BAT), TP_VBAT.TP, U1.2 (CELL), U1.3 (VDD)
VBUS: C21.1, C38.1, C42.1, C43.1, D1.5 (VBUS), IC1.A2 (IN), J3.A4_B9 (VBUS), J3.A9_B4 (VBUS), U$1.P$AD2 (VBUS)
VREG: C23.2, C24.2, C39.1, IC1.B2 (SYS), IC2.A1 (EN), IC2.A2 (VIN_1), IC2.A3 (VIN_2), TP2.TP

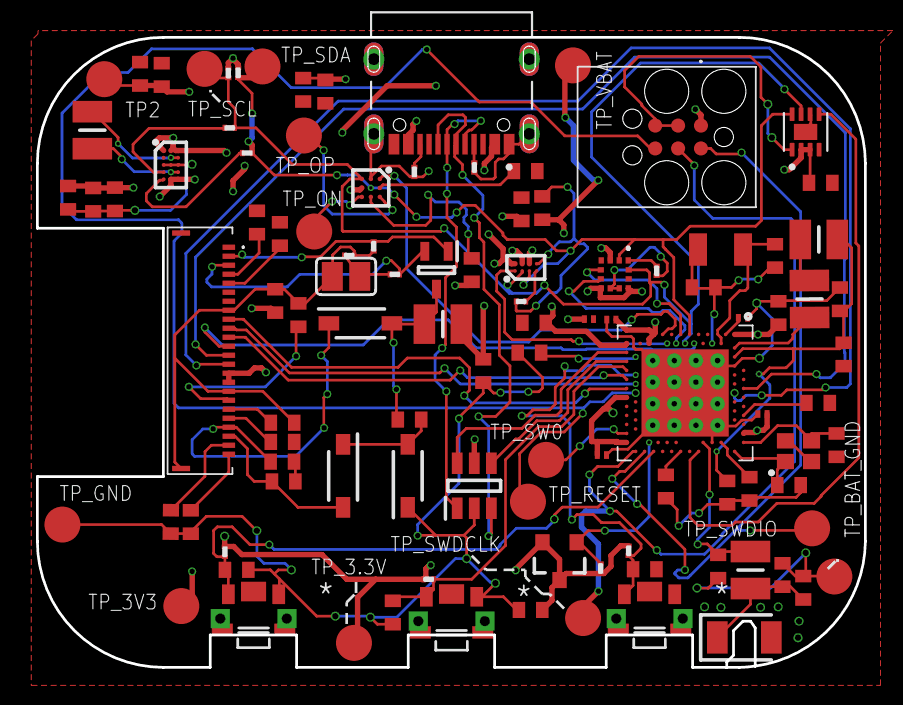
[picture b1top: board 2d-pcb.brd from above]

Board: 4 copper layers, 46.0 x 35.0 mm, 105 parts (0 on the bottom side), 70 nets.

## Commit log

2026-04-09 added files
2026-04-16 added hw files in the right format
2026-04-16 added schematic printout
2026-04-16 added renders from bottom and side of pcb
2026-04-17 Updated "Images/schema_bloc"
2026-04-17 updated README with full bom
2026-04-17 updated schematic with labels
2026-04-21 added final pictures
2026-04-21 added pictures to readme
2026-04-21 fixed README.md
2026-04-21 added final 2d pcb version

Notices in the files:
parts and their libraries:
COPYRIGHT: Copyright (C) 2025 Ultra Librarian. All rights reserved.
